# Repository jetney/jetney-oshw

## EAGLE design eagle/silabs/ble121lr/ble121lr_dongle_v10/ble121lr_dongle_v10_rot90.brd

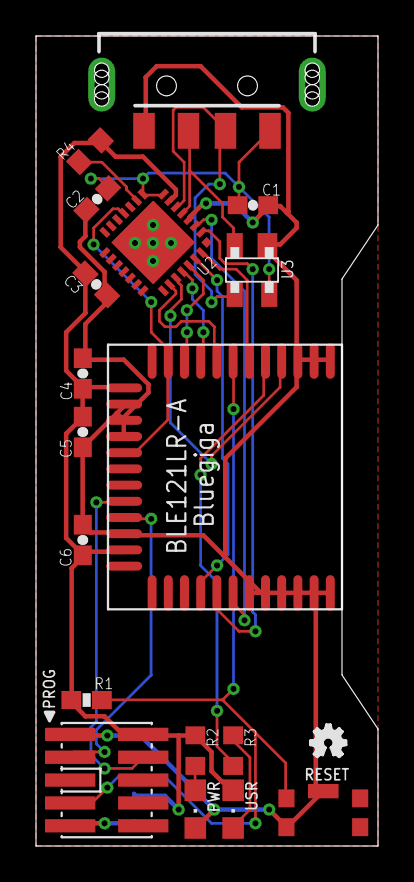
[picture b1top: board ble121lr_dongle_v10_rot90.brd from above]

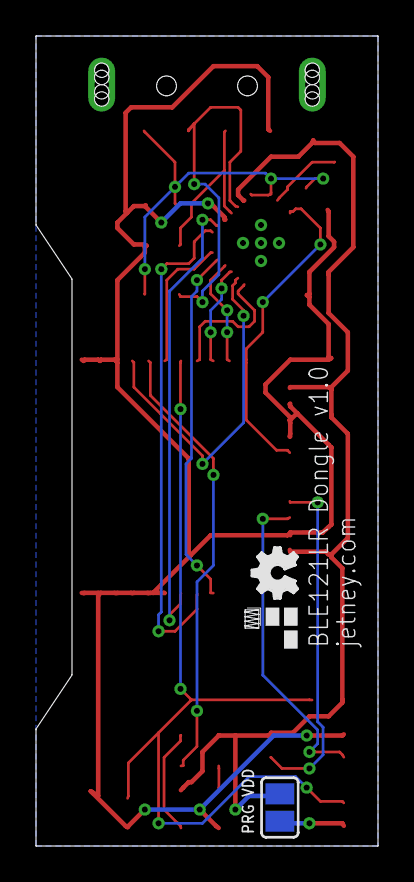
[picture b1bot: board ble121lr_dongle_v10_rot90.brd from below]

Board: 2 copper layers, 19.0 x 45.0 mm, 22 parts (3 on the bottom side), 22 nets.

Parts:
C1, C5, C6: 1uF; 0603-CAP
C2, C3: 0.1uF; 0603-CAP
C4: 4.7uF; 0603-CAP
JP1: USBA-SMD-MALE; USB-A-SMT-MALE
LOGO1: OSHW_LOGO_FILLX0100-NT; OSHW_FILLX100_NOTEXT
LOGO2: OSHW_LOGO_FILLX0070-NT; OSHW_FILLX70_NOTEXT
PROG: CONN_5-2-FTSH-V; FTSH-105-DV
PWR: GREEN; CHIPLED_0805
R1: 10K; 0603-RES
R2, R3: 470; R0603
R4: 4.7k; R0603
S1: RESET; 101-IG
SJ1: PRG VDD; SJ
U1: BLE121LR-A
U2: CP2102; MLP28
U3: SP0503BAHTG; SOT143
U$2: JETNEY-LOGO-12
USR: BLUE; CHIPLED_0805

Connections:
3.3V: C3.1, C4.1, C5.1, C6.1, PROG.2, R1.2, R2.1, R4.2, SJ1.2, U1.AVDD, U1.DVDD, U2.6, USR.A
D+: JP1.D-1, U2.4, U3.2
D-: JP1.D+1, U2.5, U3.3
GND: C1.2, C2.2, C3.2, C4.2, C5.2, C6.2, JP1.VBUS1, PROG.1, PWR.C, S1.2, S1.GND, U1.GND, U1.GND@2, U1.GND@3, U1.GND@4, U1.GND@5, U1.GND@6, U1.GND@7, U1.GND@8, U1.GND@9, U1.GND@10, U1.GND@11, U1.GND@12, U1.GND@13, U2.3, U3.1
unnamed: PWR.A, R2.2
unnamed: R3.2, USR.C
unnamed: R4.1, U2.9
NSUSPEND: U1.P0_6, U1.P1_6, U2.11
P0_0: U1.P0_0, U2.28
P0_1: R3.1, U1.P0_1
P0_2: U1.P0_2, U2.24
P0_3: U1.P0_3, U2.23
P0_4: U1.P0_4, U2.25
P0_5: U1.P0_5, U2.26
P1_2: U1.P1_2, U2.2
P1_3: U1.P1_3, U2.1
P1_4: U1.P1_4, U2.27
P2_1: PROG.4, U1.P2_1
P2_2: PROG.3, U1.P2_2
PRG_VDD: PROG.9, SJ1.1
RESET: PROG.7, R1.1, S1.1, U1.RESET
VBUS: C1.1, C2.1, JP1.GND1, U2.7, U2.8, U3.4

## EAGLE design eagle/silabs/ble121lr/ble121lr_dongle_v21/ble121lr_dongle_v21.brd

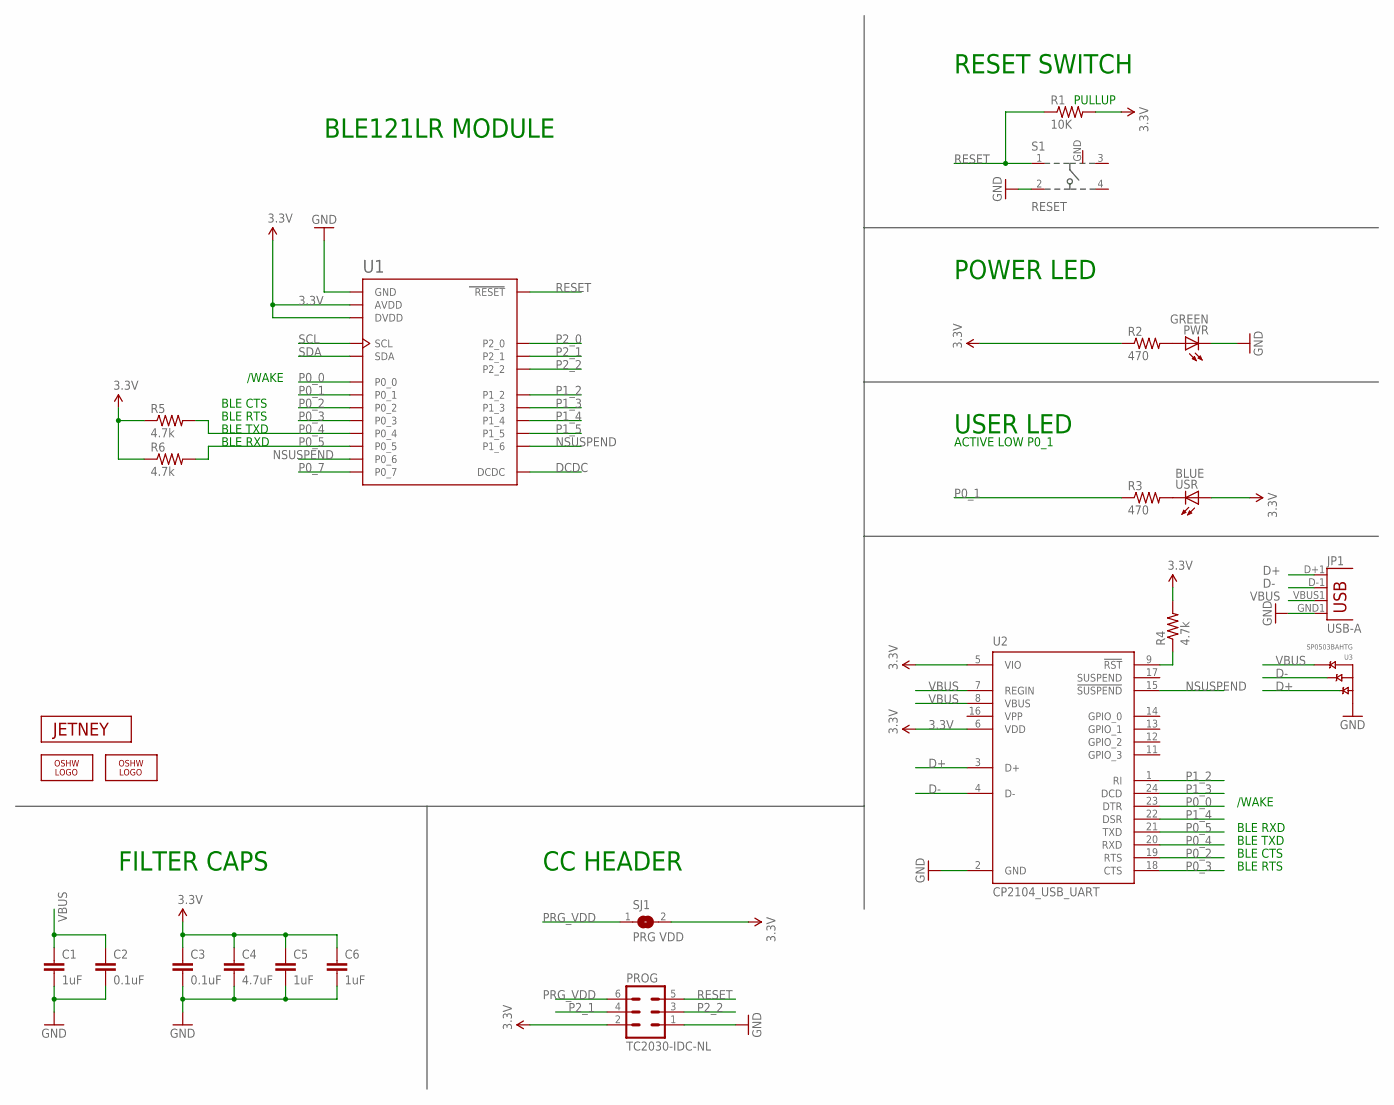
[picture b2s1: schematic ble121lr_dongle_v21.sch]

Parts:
C1, C5, C6: 1uF; 0603-CAP
C2, C3: 0.1uF; 0603-CAP
C4: 4.7uF; 0603-CAP
JP1: USB-A; USB-A-SMT-MALE-MOLEX
LOGO1: OSHW_LOGO_FILLX0100-NT; OSHW_FILLX100_NOTEXT
LOGO2: OSHW_LOGO_FILLX0070-NT; OSHW_FILLX70_NOTEXT
PROG: TC2030-IDC-NL
PWR: GREEN; CHIPLED_0805
R1: 10K; 0603-RES
R2, R3: 470; R0603
R4, R5, R6: 4.7k; R0603
S1: RESET; 101-IG
SJ1: PRG VDD; SJ
U1: BLE121LR-A
U2: CP2104_USB_UART; QFN-24_ALT1.PAC
U3: SP0503BAHTG; SOT143
U$2: JETNEY-LOGO-12
USR: BLUE; CHIPLED_0805

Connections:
3.3V: C3.1, C4.1, C5.1, C6.1, PROG.2, R1.2, R2.1, R4.2, R5.1, R6.1, SJ1.2, U1.AVDD, U1.DVDD, U2.5 (VIO), U2.6 (VDD), USR.A
D+: JP1.D+1 (D+), U2.3 (D+), U3.2 (A)
D-: JP1.D-1 (D-), U2.4 (D-), U3.3 (B)
DCDC: U1.DCDC
GND: C1.2, C2.2, C3.2, C4.2, C5.2, C6.2, JP1.GND1 (GND), PROG.1, PWR.C, S1.2, S1.GND, U1.GND, U1.GND@2 (GND), U1.GND@3 (GND), U1.GND@4 (GND), U1.GND@5 (GND), U1.GND@6 (GND), U1.GND@7 (GND), U1.GND@8 (GND), U1.GND@9 (GND), U1.GND@10 (GND), U1.GND@11 (GND), U1.GND@12 (GND), U1.GND@13 (GND), U2.2 (GND), U3.1 (GND)
unnamed: PWR.A, R2.2
unnamed: R3.2, USR.C
unnamed: R4.1, U2.9 (!RST)
NSUSPEND: U1.P0_6, U1.P1_6, U2.15 (!SUSPEND)
P0_0: U1.P0_0, U2.23 (DTR)
P0_1: R3.1, U1.P0_1
P0_2: U1.P0_2, U2.19 (RTS)
P0_3: U1.P0_3, U2.18 (CTS)
P0_4: R5.2, U1.P0_4, U2.20 (RXD)
P0_5: R6.2, U1.P0_5, U2.21 (TXD)
P0_7: U1.P0_7
P1_2: U1.P1_2, U2.1 (RI)
P1_3: U1.P1_3, U2.24 (DCD)
P1_4: U1.P1_4, U2.22 (DSR)
P1_5: U1.P1_5
P2_0: U1.P2_0
P2_1: PROG.4, U1.P2_1
P2_2: PROG.3, U1.P2_2
PRG_VDD: PROG.6, SJ1.1
RESET: PROG.5, R1.1, S1.1, U1.RESET
SCL: U1.SCL
SDA: U1.SDA
VBUS: C1.1, C2.1, JP1.VBUS1 (VBUS), U2.7 (REGIN), U2.8 (VBUS), U3.4 (C)
VPP: U2.16 (VPP)

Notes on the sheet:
POWER LED
USER LED
CC HEADER
BLE121LR MODULE
RESET SWITCH
PULLUP
FILTER CAPS
BLE RXD
BLE TXD
BLE CTS
BLE RTS
/WAKE
ACTIVE LOW P0_1

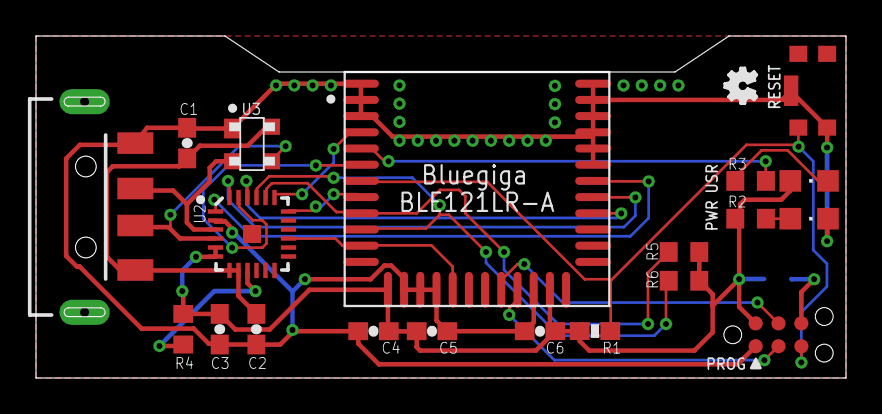
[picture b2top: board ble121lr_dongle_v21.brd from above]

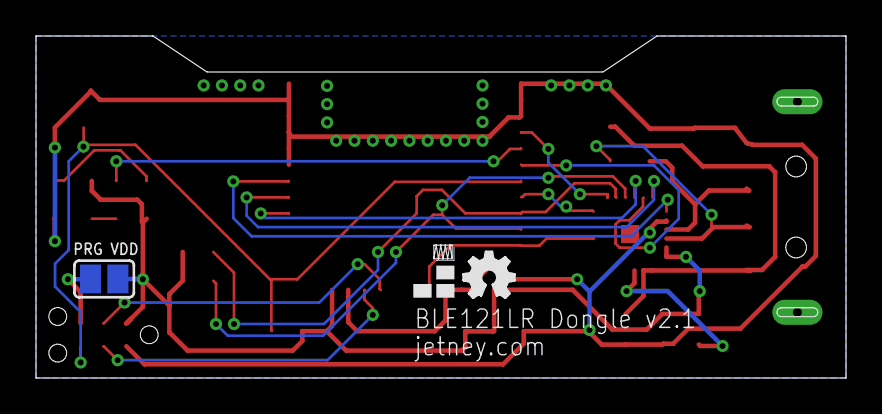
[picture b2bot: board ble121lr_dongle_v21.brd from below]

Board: 2 copper layers, 45.0 x 19.0 mm, 24 parts (3 on the bottom side), 22 nets.

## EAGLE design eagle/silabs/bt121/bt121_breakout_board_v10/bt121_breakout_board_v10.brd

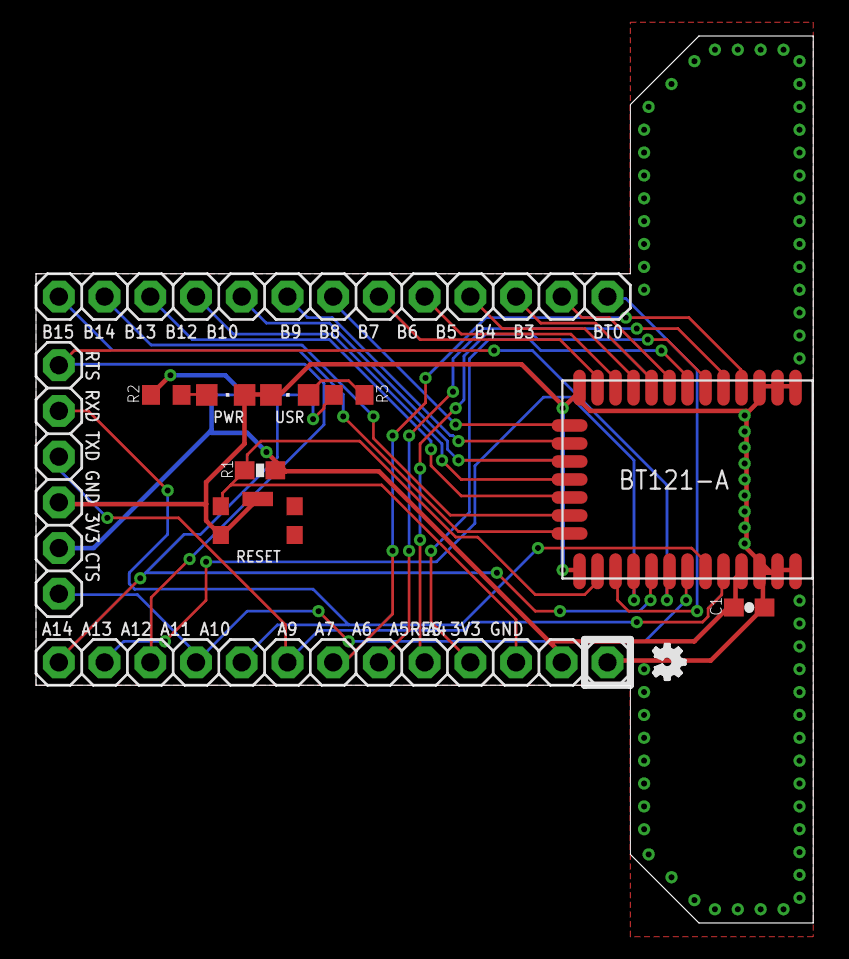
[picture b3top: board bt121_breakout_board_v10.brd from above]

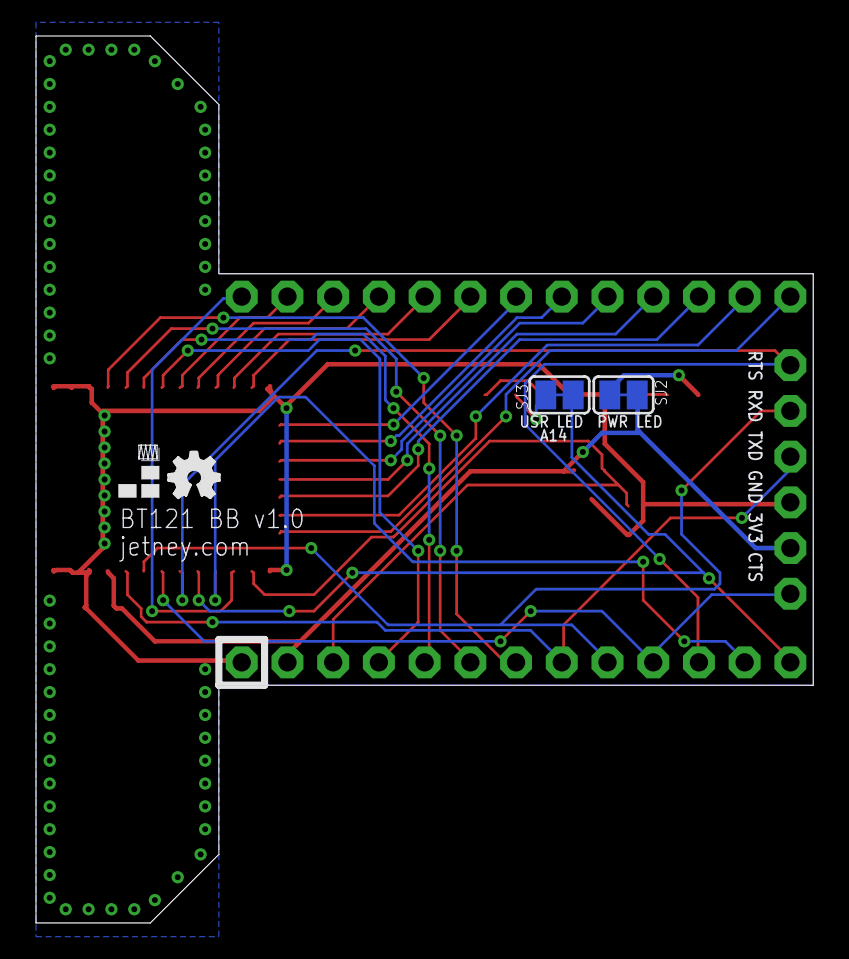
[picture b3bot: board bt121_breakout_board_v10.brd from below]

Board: 2 copper layers, 43.2 x 49.3 mm, 16 parts (4 on the bottom side), 30 nets.

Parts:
C1: 1uF; 0603-CAP
JP1, JP2: 1X13
JP3: 1X06
LOGO1: OSHW_LOGO_FILLX0100-NT; OSHW_FILLX100_NOTEXT
LOGO2: OSHW_LOGO_FILLX0070-NT; OSHW_FILLX70_NOTEXT
PWR: GREEN; CHIPLED_0805
R1: 10K; 0603-RES
R2, R3: 470; R0603
S1: RESET; 101-IG
SJ2: PWR LED; SJ
SJ3: USR LED; SJ
U1: BT121-A
U$2: JETNEY-LOGO-12
USR: BLUE; CHIPLED_0805

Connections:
3.3V: C1.1, JP2.2, JP3.5, R1.2, SJ2.1, U1.VDD
BOOT0: JP1.1, U1.BOOT0
GND: C1.2, JP2.1, JP3.4, PWR.C, S1.2, S1.GND, U1.GND, U1.GND@2, U1.GND@3, U1.GND@4, U1.GND@5, U1.GND@6, U1.GND@7, U1.RF, USR.C
unnamed: PWR.A, R2.2
unnamed: R2.1, SJ2.2
unnamed: R3.2, USR.A
unnamed: R3.1, SJ3.2
PA4: JP2.4, U1.PA4
PA5: JP2.5, U1.PA5
PA6: JP2.6, U1.PA6
PA7: JP2.7, U1.PA7
PA9: JP2.8, JP3.3, U1.PA9
PA10: JP2.9, JP3.2, U1.PA10
PA11: JP2.10, JP3.6, U1.PA11
PA12: JP2.11, JP3.1, U1.PA12
PA13: JP2.12, U1.PA13
PA14: JP2.13, SJ3.1, U1.PA14
PB3: JP1.2, U1.PB3
PB4: JP1.3, U1.PB4
PB5: JP1.4, U1.PB5
PB6: JP1.5, U1.PB6
PB7: JP1.6, U1.PB7
PB8: JP1.7, U1.PB8
PB9: JP1.8, U1.PB9
PB10: JP1.9, U1.PB10
PB12: JP1.10, U1.PB12
PB13: JP1.11, U1.PB13
PB14: JP1.12, U1.PB14
PB15: JP1.13, U1.PB15
RESET: JP2.3, R1.1, S1.1, U1.RESET

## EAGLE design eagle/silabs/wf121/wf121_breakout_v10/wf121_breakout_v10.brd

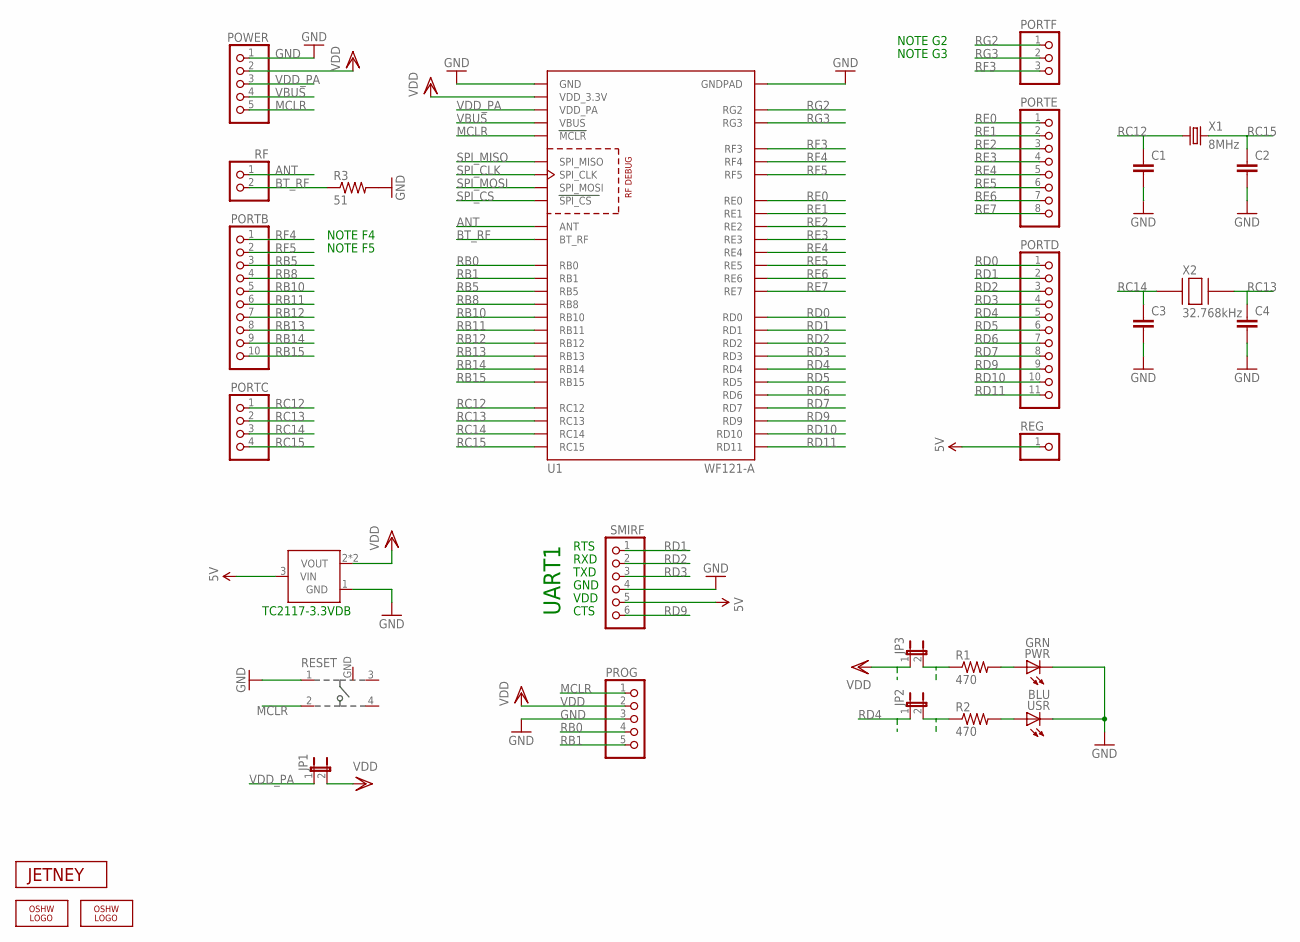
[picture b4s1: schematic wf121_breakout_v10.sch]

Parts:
C1, C2, C3, C4: CAP0603-CAP; 0603-CAP
JP1: JUMPER-2PTH; 1X02
JP2, JP3: JUMPER-2SMD-NC; SJ_2S
LOGO1, LOGO2: OSHW_LOGO_FILLX0100-NT; OSHW_FILLX100_NOTEXT
PORTB: PINHD-1X10; 1X10
PORTC: PINHD-1X4; 1X04
PORTD: PINHD-1X11; 1X11
PORTE: PINHD-1X8; 1X08
PORTF: PINHD-1X3; 1X03
POWER: PINHD-1X5; 1X05
PROG: PINHD-1X5; 1X05
PWR: GRN; CHIPLED_0805
R1, R2: 470; 0603-RES
R3: 51; 0603-RES
REG: PINHD-1X1; 1X01
RESET: 101-IG
RF: PINHD-1X2; 1X02
SMIRF: PINHD-1X6; 1X06
U1: WF121-A
U2: VREGAP1117; SOT223
U$4: JETNEY-LOGO-12
USR: BLU; CHIPLED_0805
X1: 8MHz; CRYSTAL-TXC-7A
X2: 32.768kHz; ABS07

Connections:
5V: REG.1, SMIRF.5, U2.3 (VIN)
ANT: RF.1, U1.ANT
BT_RF: R3.1, RF.2, U1.BT_RF
GND: C1.2, C2.2, C3.2, C4.2, POWER.1, PROG.3, PWR.C, R3.2, RESET.1, RESET.GND, SMIRF.4, U1.GND, U1.GND@2 (GND), U1.GND@3 (GND), U1.GND@4 (GND), U1.GND@5 (GND), U1.GND@6 (GND), U1.GNDPAD, U2.1 (GND), USR.C
MCLR: POWER.5, PROG.1, RESET.2, U1.MCLR
unnamed: PWR.A, R1.2
unnamed: JP2.2, R2.1
unnamed: R2.2, USR.A
unnamed: JP3.2, R1.1
RB0: PROG.4, U1.RB0
RB1: PROG.5, U1.RB1
RB5: PORTB.3, U1.RB5
RB8: PORTB.4, U1.RB8
RB10: PORTB.5, U1.RB10
RB11: PORTB.6, U1.RB11
RB12: PORTB.7, U1.RB12
RB13: PORTB.8, U1.RB13
RB14: PORTB.9, U1.RB14
RB15: PORTB.10, U1.RB15
RC12: C1.1, PORTC.1, U1.RC12, X1.P$1 (1)
RC13: C4.1, PORTC.2, U1.RC13, X2.X2
RC14: C3.1, PORTC.3, U1.RC14, X2.X1
RC15: C2.1, PORTC.4, U1.RC15, X1.P$2 (2)
RD0: PORTD.1, U1.RD0
RD1: PORTD.2, SMIRF.1, U1.RD1
RD2: PORTD.3, SMIRF.2, U1.RD2
RD3: PORTD.4, SMIRF.3, U1.RD3
RD4: JP2.1, PORTD.5, U1.RD4
RD5: PORTD.6, U1.RD5
RD6: PORTD.7, U1.RD6
RD7: PORTD.8, U1.RD7
RD9: PORTD.9, SMIRF.6, U1.RD9
RD10: PORTD.10, U1.RD10
RD11: PORTD.11, U1.RD11
RE0: PORTE.1, U1.RE0
RE1: PORTE.2, U1.RE1
RE2: PORTE.3, U1.RE2
RE3: PORTE.4, U1.RE3
RE4: PORTE.5, U1.RE4
RE5: PORTE.6, U1.RE5
RE6: PORTE.7, U1.RE6
RE7: PORTE.8, U1.RE7
RF3: PORTF.3, U1.RF3
RF4: PORTB.1, U1.RF4
RF5: PORTB.2, U1.RF5
RG2: PORTF.1, U1.RG2
RG3: PORTF.2, U1.RG3
SPI_CLK: U1.SPI_CLK
SPI_CS: U1.SPI_CS
SPI_MISO: U1.SPI_MISO
SPI_MOSI: U1.SPI_MOSI
VBUS: POWER.4, U1.VBUS
VDD: JP1.2, JP3.1, POWER.2, PROG.2, U1.VDD_3.3V, U2.2 (VOUT), U2.4 (VOUT)
VDD_PA: JP1.1, POWER.3, U1.VDD_PA

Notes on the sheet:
TXD
CTS
RTS
RXD
UART1
GND
VDD
NOTE F4
NOTE F5
NOTE G2
NOTE G3
TC2117-3.3VDB

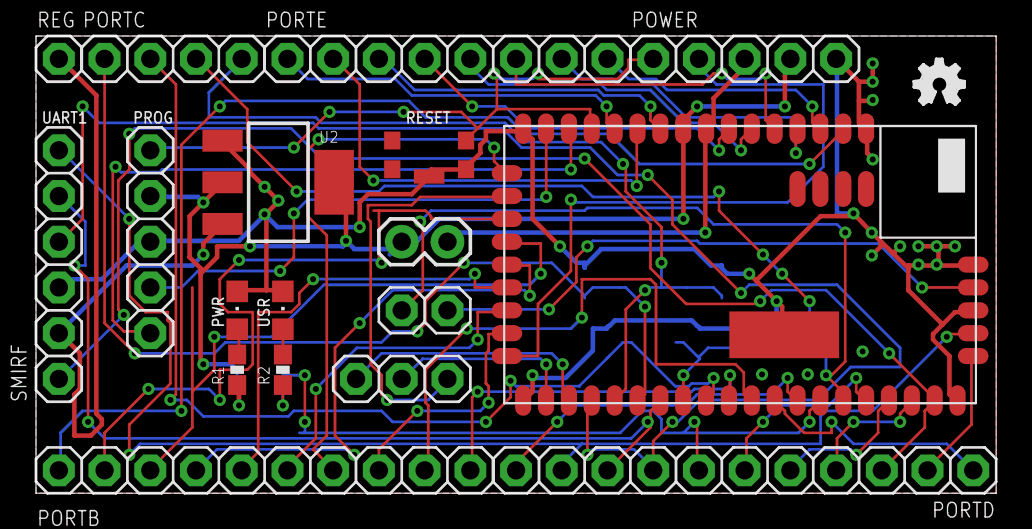
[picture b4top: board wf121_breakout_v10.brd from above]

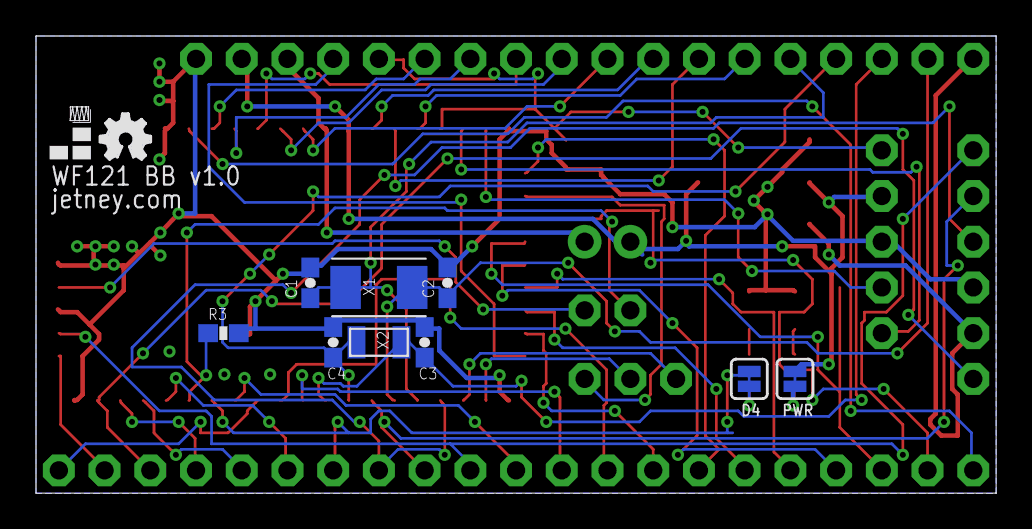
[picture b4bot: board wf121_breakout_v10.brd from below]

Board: 2 copper layers, 53.3 x 25.4 mm, 30 parts (11 on the bottom side), 50 nets.

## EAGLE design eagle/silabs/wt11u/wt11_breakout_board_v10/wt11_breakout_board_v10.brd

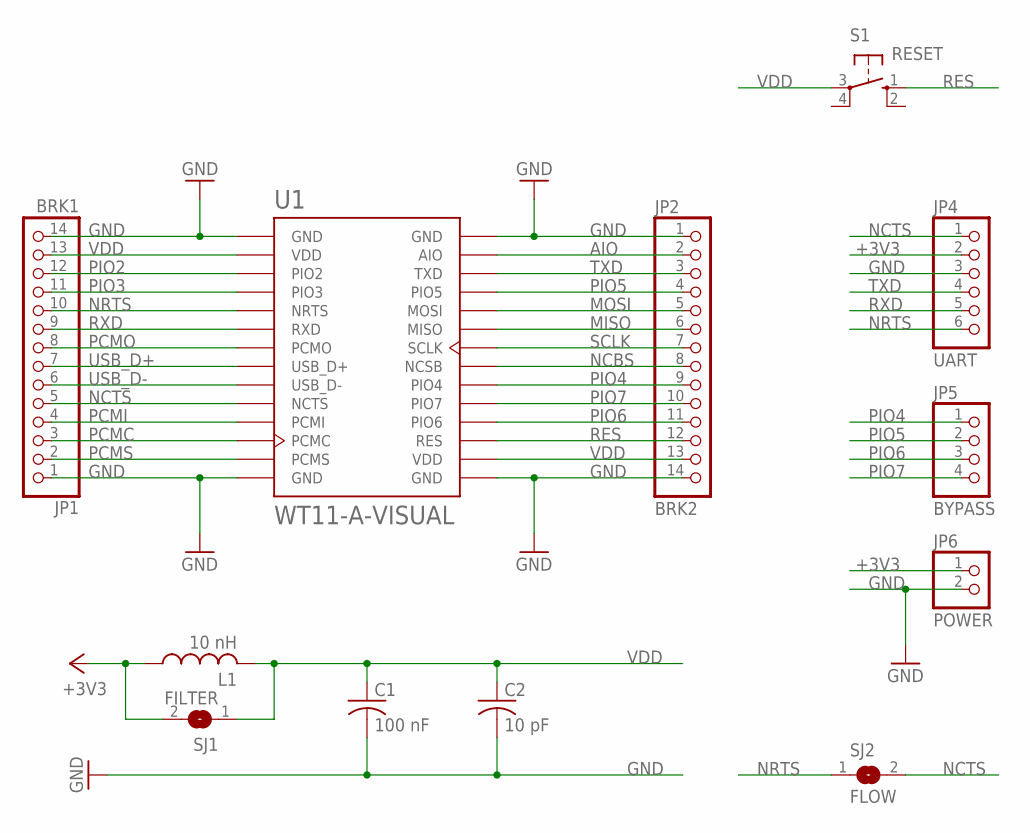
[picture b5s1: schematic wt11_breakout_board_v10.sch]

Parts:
C1: 100 nF; C025-025X050
C2: 10 pF; C025-025X050
JP1: BRK1; 1X14
JP2: BRK2; 1X14
JP4: UART; 1X06
JP5: BYPASS; 1X04
JP6: POWER; 1X02
L1: 10 nH; 0204/7
S1: RESET; B3F-10XX
SJ1: FILTER; SJ
SJ2: FLOW; SJ
U1: WT11-A-VISUAL; WT11-A

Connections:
+3V3: JP4.2, JP6.1, L1.1, SJ1.2
AIO: JP2.2, U1.AIO
GND: C1.2, C2.2, JP1.1, JP1.14, JP2.1, JP2.14, JP4.3, JP6.2, U1.GND1 (GND), U1.GND2 (GND), U1.GND3 (GND), U1.GND4 (GND)
MISO: JP2.6, U1.MISO
MOSI: JP2.5, U1.MOSI
NCBS: JP2.8, U1.NCSB
NCTS: JP1.5, JP4.1, SJ2.2, U1.NCTS
NRTS: JP1.10, JP4.6, SJ2.1, U1.NRTS
PCMC: JP1.3, U1.PCMC
PCMI: JP1.4, U1.PCMI
PCMO: JP1.8, U1.PCMO
PCMS: JP1.2, U1.PCMS
PIO2: JP1.12, U1.PIO2
PIO3: JP1.11, U1.PIO3
PIO4: JP2.9, JP5.1, U1.PIO4
PIO5: JP2.4, JP5.2, U1.PIO5
PIO6: JP2.11, JP5.3, U1.PIO6
PIO7: JP2.10, JP5.4, U1.PIO7
RES: JP2.12, S1.1 (S), U1.RES
RXD: JP1.9, JP4.5, U1.RXD
SCLK: JP2.7, U1.SCLK
TXD: JP2.3, JP4.4, U1.TXD
USB_D+: JP1.7, U1.USB_D+
USB_D-: JP1.6, U1.USB_D-
VDD: C1.1, C2.1, JP1.13, JP2.13, L1.2, S1.3, SJ1.1, U1.VDD1 (VDD), U1.VDD2 (VDD)

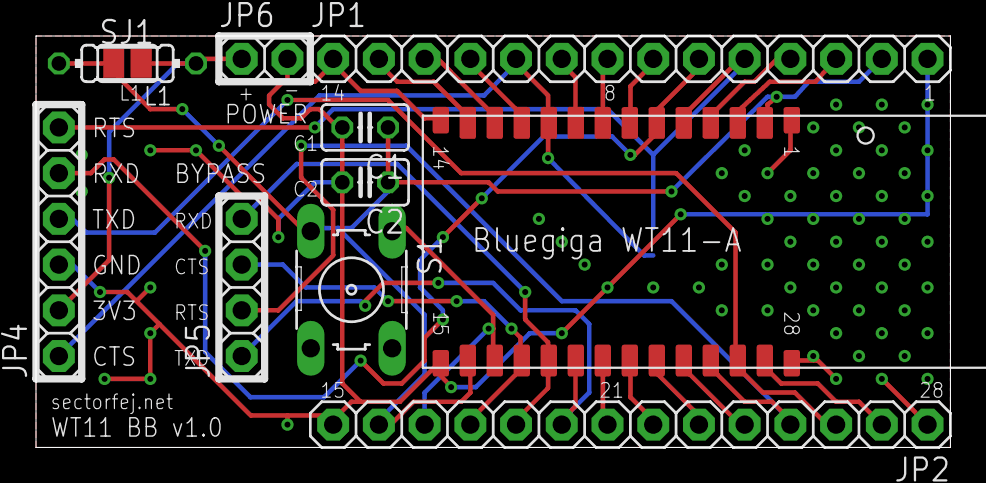
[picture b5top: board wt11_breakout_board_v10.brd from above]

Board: 2 copper layers, 50.8 x 22.9 mm, 12 parts (1 on the bottom side), 25 nets.

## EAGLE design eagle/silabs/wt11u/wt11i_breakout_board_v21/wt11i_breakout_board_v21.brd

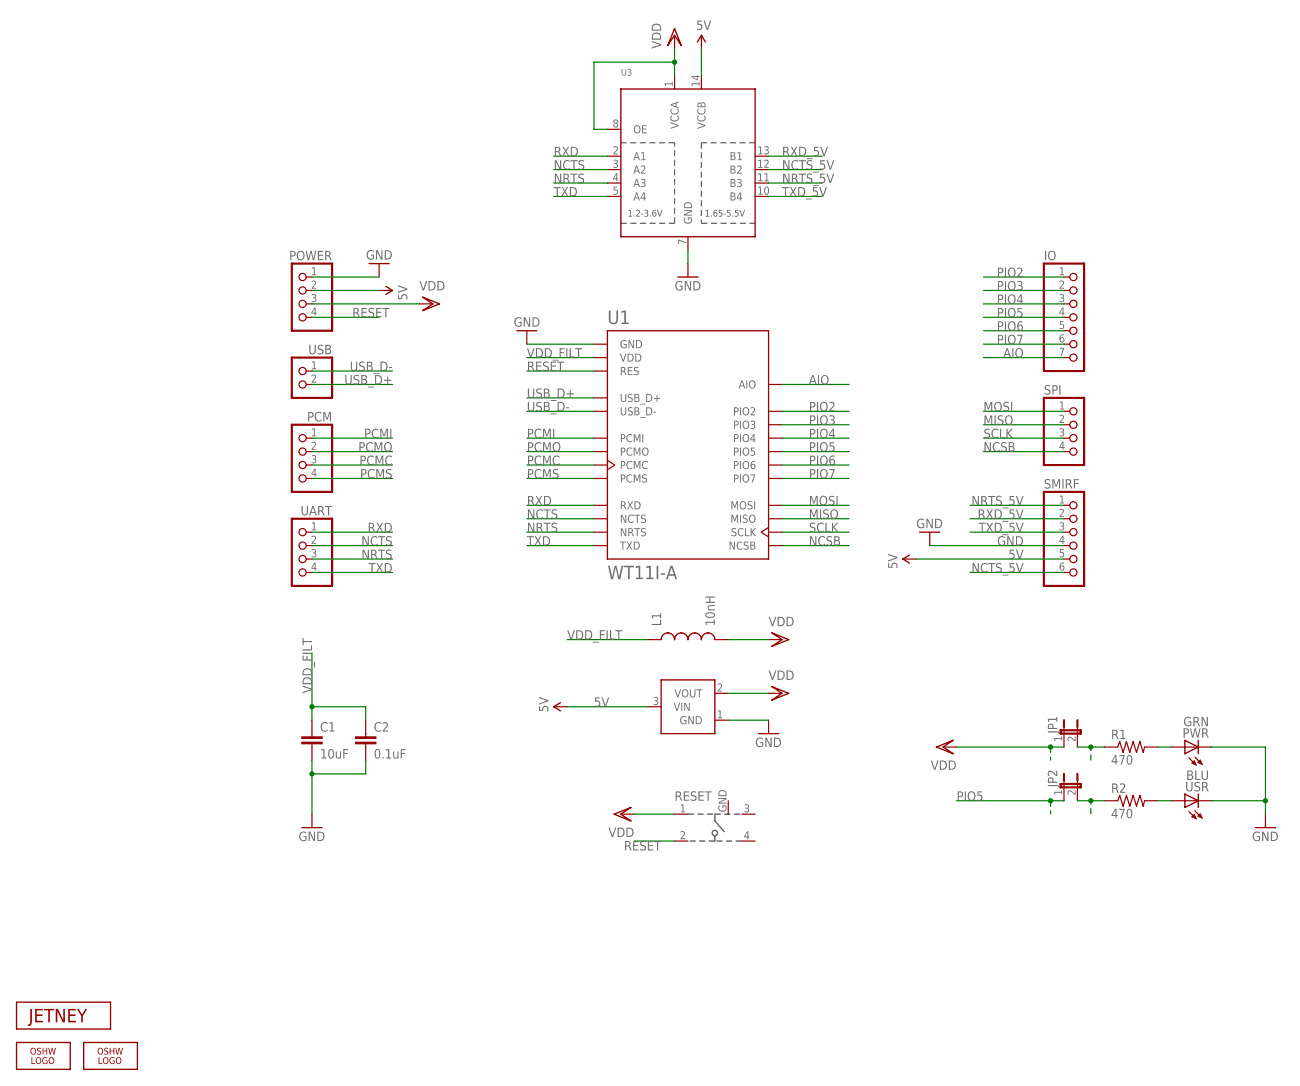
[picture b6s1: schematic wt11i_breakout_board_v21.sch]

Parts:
C1: 10uF; 0603-CAP
C2: 0.1uF; 0603-CAP
IO: PINHD-1X7; 1X07
JP1, JP2: JUMPER-2SMD-NC; SJ_2S
L1: 10nH; 0603
LOGO1, LOGO3: OSHW_LOGO_FILLX0070-NT; OSHW_FILLX70_NOTEXT
PCM: PINHD-1X4; 1X04
POWER: PINHD-1X4; 1X04
PWR: GRN; CHIPLED_0805
R1, R2: 470; 0603-RES
RESET: 101-IG
SMIRF: PINHD-1X6; 1X06
SPI: PINHD-1X4; 1X04
U1: WT11I-A
U2: MCP1700; SOT23-3
U3: TXB0104PWR; TSSOP14
U$2: JETNEY-LOGO-12
UART: PINHD-1X4; 1X04
USB: PINHD-1X2; 1X02
USR: BLU; CHIPLED_0805

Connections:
5V: POWER.2, SMIRF.5, U2.3 (VIN), U3.14 (VCCB)
AIO: IO.7, U1.AIO
GND: C1.2, C2.2, POWER.1, PWR.C, RESET.GND, SMIRF.4, U1.GND, U1.GND@2 (GND), U1.GND@3 (GND), U1.GND@4 (GND), U2.1 (GND), U3.7 (GND), USR.C
MISO: SPI.2, U1.MISO
MOSI: SPI.1, U1.MOSI
unnamed: PWR.A, R1.2
unnamed: R2.2, USR.A
unnamed: JP2.2, R2.1
NCSB: SPI.4, U1.NCSB
NCTS: U1.NCTS, U3.3 (A2), UART.2
NCTS_5V: SMIRF.6, U3.12 (B2)
NRTS: U1.NRTS, U3.4 (A3), UART.3
NRTS_5V: SMIRF.1, U3.11 (B3)
PCMC: PCM.3, U1.PCMC
PCMI: PCM.1, U1.PCMI
PCMO: PCM.2, U1.PCMO
PCMS: PCM.4, U1.PCMS
PIO2: IO.1, U1.PIO2
PIO3: IO.2, U1.PIO3
PIO4: IO.3, U1.PIO4
PIO5: IO.4, JP2.1, U1.PIO5
PIO6: IO.5, U1.PIO6
PIO7: IO.6, U1.PIO7
RESET: POWER.4, RESET.2, U1.RES
RXD: U1.RXD, U3.2 (A1), UART.1
RXD_5V: SMIRF.2, U3.13 (B1)
SCLK: SPI.3, U1.SCLK
TXD: U1.TXD, U3.5 (A4), UART.4
TXD_5V: SMIRF.3, U3.10 (B4)
USB_D+: U1.USB_D+, USB.2
USB_D-: U1.USB_D-, USB.1
VDD: JP1.1, L1.2, POWER.3, RESET.1, U2.2 (VOUT), U3.1 (VCCA), U3.8 (OE)
VDDJP1: JP1.2, R1.1
VDD_FILT: C1.1, C2.1, L1.1, U1.VDD, U1.VDD@2 (VDD)

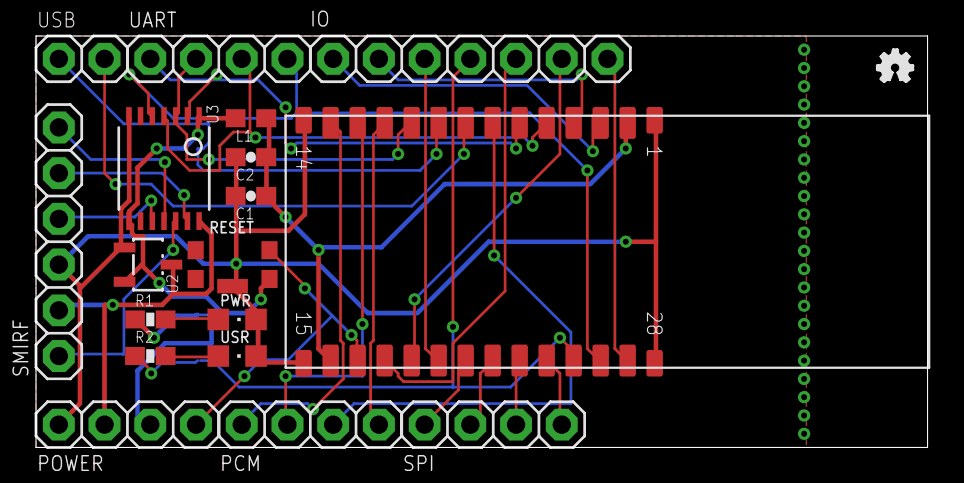
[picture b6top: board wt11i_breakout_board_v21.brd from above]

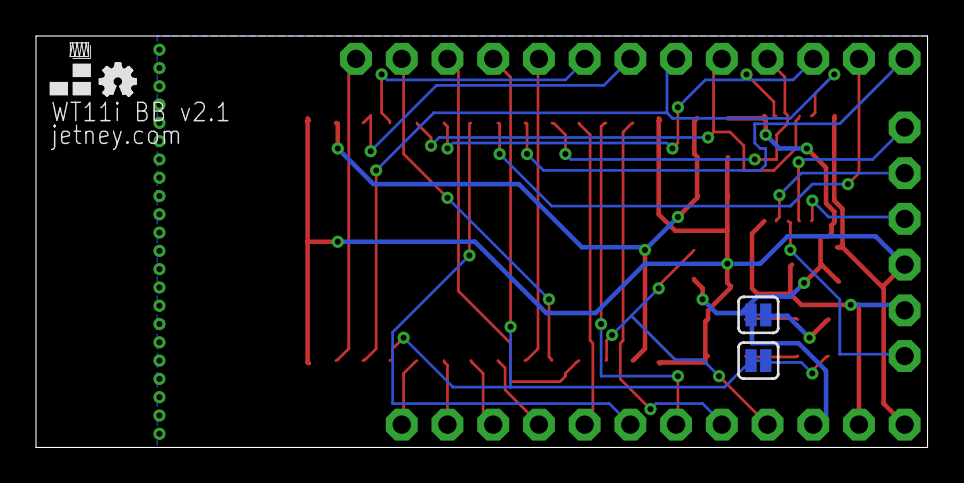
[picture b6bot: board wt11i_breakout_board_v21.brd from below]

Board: 2 copper layers, 49.5 x 22.9 mm, 23 parts (4 on the bottom side), 34 nets.

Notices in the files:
parts and their libraries:
SparkFun: Licensing: CC v3.0 Share-Alike You are welcome to use this library for commercial purposes.
SparkFun-DigitalIC: Licensing: Creative Commons ShareAlike 4.0 International - https://creativecommons.org/licenses/by-sa/4.0
